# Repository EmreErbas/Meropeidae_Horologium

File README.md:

# Meropeidae Horologium

---
>**This project contains sub-modules. Clone the project recursively**
>
>`git clone --recurse-submodules git@github.com:EmreErbas/Meropeidae_Horologium.git`

---

## Meropeidae Horologium

It is a computer, consisting of a 16x36 resolution screen inspired by [Nixie Tubes](https://en.wikipedia.org/wiki/Nixie_tube), made of single-color LEDs selected according to the wavelength of the light emitted in the excitation of neon gas, and a WiFi-connected controller that drives it.

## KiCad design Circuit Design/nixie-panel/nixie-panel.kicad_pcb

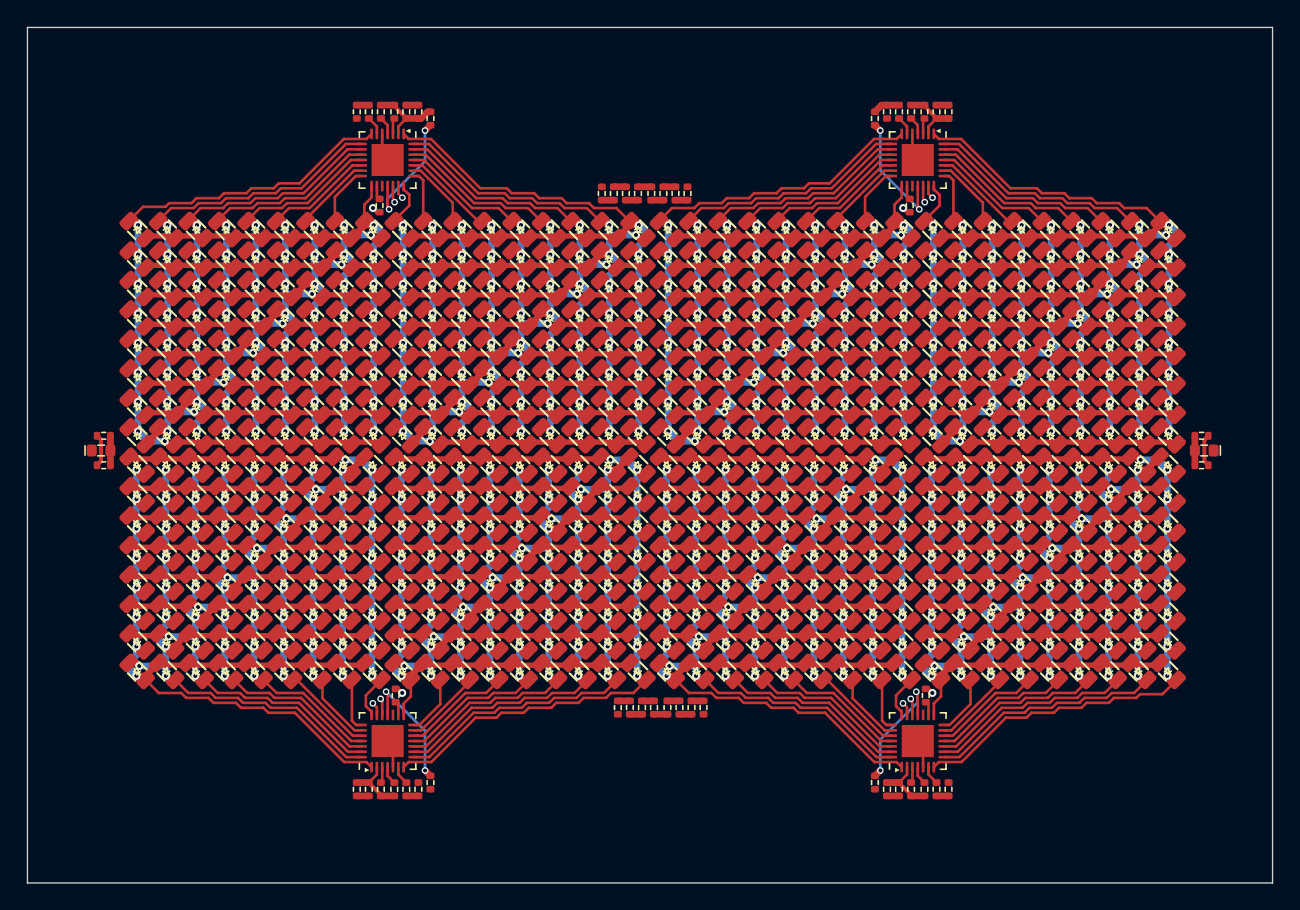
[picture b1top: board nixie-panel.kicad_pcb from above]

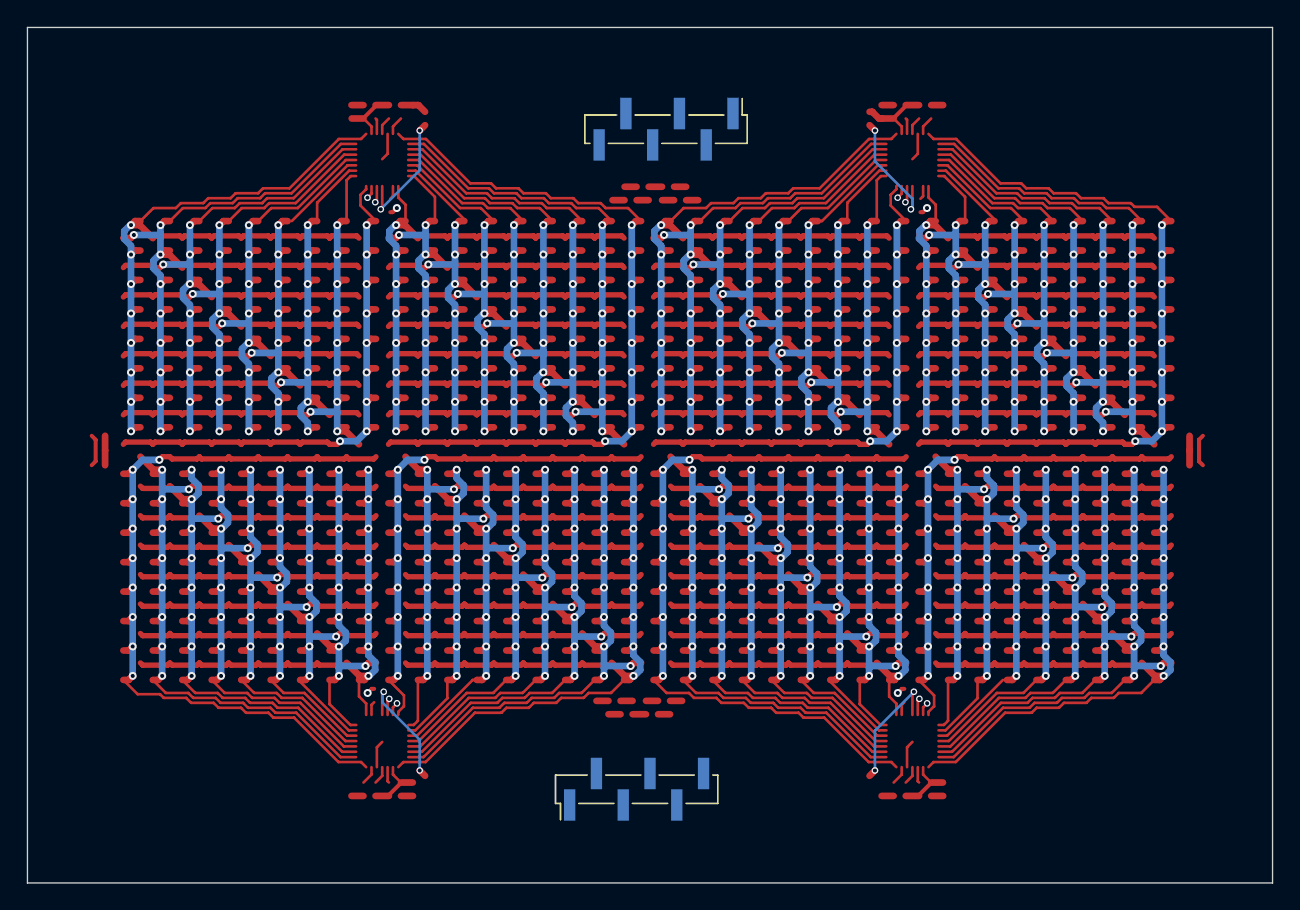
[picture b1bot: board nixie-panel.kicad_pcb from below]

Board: 2 copper layers, 93.0 x 63.9 mm, 636 parts (2 on the bottom side), 108 nets.

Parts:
C24, C25, C26, C30, C34, C38: 1uF; C-0402
C27, C28, C29, C31, C32, C33, C35, C36, C37, C39, C40, C41: 100nF; C-0402
D3, D4, D5, D6, D7, D8, D9, D10, D11, D12, D13, D14, D15, D16, D17, D18, D19, D20, D21, D22, D23, D24, D25, D26, D27, D28, D29, D30, D31, D32, D33, D34, D35, D36, D37, D38, D39, D40, D41, D42, D43, D44, D45, D46, D47, D48, D49, D50, D51, D52, D53, D54, D55, D56, D57, D58, D59, D60, D61, D62, D63, D64, D65, D66, D67, D68, D69, D70, D71, D72, D73, D74, D75, D76, D77, D78, D79, D80, D81, D82, D83, D84, D85, D86, D87, D88, D89, D90, D91, D92, D93, D94, D95, D96, D97, D98, D99, D100, D101, D102, D103, D104, D105, D106, D107, D108, D109, D110, D111, D112, D113, D114, D115, D116, D117, D118, D119, D120, D121, D122, D123, D124, D125, D126, D127, D128, D129, D130, D131, D132, D133, D134, D135, D136, D137, D138, D139, D140, D141, D142, D143, D144, D145, D146, D147, D148, D149, D150, D151, D152, D153, D154, D155, D156, D157, D158, D159, D160, D161, D162, D163, D164, D165, D166, D167, D168, D169, D170, D171, D172, D173, D174, D175, D176, D177, D178, D179, D180, D181, D182, D183, D184, D185, D186, D187, D188, D189, D190, D191, D192, D193, D194, D195, D196, D197, D198, D199, D200, D201, D202, D203, D204, D205, D206, D207, D208, D209, D210, D211, D212, D213, D214, D215, D216, D217, D218, D219, D220, D221, D222, D223, D224, D225, D226, D227, D228, D229, D230, D231, D232, D233, D234, D235, D236, D237, D238, D239, D240, D241, D242, D243, D244, D245, D246, D247, D248, D249, D250, D251, D252, D253, D254, D255, D256, D257, D258, D259, D260, D261, D262, D263, D264, D265, D266, D267, D268, D269, D270, D271, D272, D273, D274, D275, D276, D277, D278, D279, D280, D281, D282, D283, D284, D285, D286, D287, D288, D289, D290, D291, D292, D293, D294, D295, D296, D297, D298, D299, D300, D301, D302, D303, D304, D305, D306, D307, D308, D309, D310, D311, D312, D313, D314, D315, D316, D317, D318, D319, D320, D321, D322, D323, D324, D325, D326, D327, D328, D329, D330, D331, D332, D333, D334, D335, D336, D337, D338, D339, D340, D341, D342, D343, D344, D345, D346, D347, D348, D349, D350, D351, D352, D353, D354, D355, D356, D357, D358, D359, D360, D361, D362, D363, D364, D365, D366, D367, D368, D369, D370, D371, D372, D373, D374, D375, D376, D377, D378, D379, D380, D381, D382, D383, D384, D385, D386, D387, D388, D389, D390, D391, D392, D393, D394, D395, D396, D397, D398, D399, D400, D401, D402, D403, D404, D405, D406, D407, D408, D409, D410, D411, D412, D413, D414, D415, D416, D417, D418, D419, D420, D421, D422, D423, D424, D425, D426, D427, D428, D429, D430, D431, D432, D433, D434, D435, D436, D437, D438, D439, D440, D441, D442, D443, D444, D445, D446, D447, D448, D449, D450, D451, D452, D453, D454, D455, D456, D457, D458, D459, D460, D461, D462, D463, D464, D465, D466, D467, D468, D469, D470, D471, D472, D473, D474, D475, D476, D477, D478, D479, D480, D481, D482, D483, D484, D485, D486, D487, D488, D489, D490, D491, D492, D493, D494, D495, D496, D497, D498, D499, D500, D501, D502, D503, D504, D505, D506, D507, D508, D509, D510, D511, D512, D513, D514, D515, D516, D517, D518, D519, D520, D521, D522, D523, D524, D525, D526, D527, D528, D529, D530, D531, D532, D533, D534, D535, D536, D537, D538, D539, D540, D541, D542, D543, D544, D545, D546, D547, D548, D549, D550, D551, D552, D553, D554, D555, D556, D557, D558, D559, D560, D561, D562, D563, D564, D565, D566, D567, D568, D569, D570, D571, D572, D573, D574, D575, D576, D577, D578: LED_Y_L; LED-0805
J1, J2: Conn_01x06; PinHeader_1x06_P2.00mm_Vertical_SMD_Pin1Left
R15, R16: 2K; R-0402
R17, R18, R19, R20, R27, R28, R29, R30, R37, R38, R39, R40, R47, R48, R49, R50: 10K; R-0402
R21, R22, R31, R32, R41, R42, R51, R52: 1R; R-0402
R25, R35, R45, R55: 0R; R-0402
R26, R36, R46, R56: 18K; R-0402
S1, S2: AmbLightSns; LED-0603
U4, U5, U6, U7: IS31FL3731; QFN-28-EP

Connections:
+3V3: C26.1, C27.1, C28.1, C30.1, C31.1, C32.1, C34.1, C35.1, C36.1, C38.1, C39.1, C40.1, J1.6, J2.6, R17.1, R18.1, R19.1, R20.1, R25.1, R27.1, R28.1, R29.1, R30.1, R35.1, R37.1, R38.1, R39.1, R40.1, R47.1, R48.1, R49.1, R50.1, S1.1, S2.1, U4.2 (VCC), U5.2 (VCC), U6.2 (VCC), U7.2 (VCC)
/I2C0-SCL: J1.3, R22.1, R42.1
/I2C0-SDA: J1.4, R21.1, R41.1
/I2C1-SCL: J2.3, R32.1, R52.1
/I2C1-SDA: J2.4, R31.1, R51.1
/LightSense1: C24.1, J1.2, R15.1, S1.2
/LightSense2: C25.1, J1.5, R16.1, S2.2
/region1/LED Driver/CA1: D3.1 (K), D4.1 (K), D5.1 (K), D6.1 (K), D7.1 (K), D8.1 (K), D9.1 (K), D10.1 (K), D19.2 (A), D35.2 (A), D51.2 (A), D67.2 (A), D83.2 (A), D99.2 (A), D115.2 (A), D131.2 (A), U4.21 (CA1)
/region1/LED Driver/CA2: D3.2 (A), D19.1 (K), D20.1 (K), D21.1 (K), D22.1 (K), D23.1 (K), D24.1 (K), D25.1 (K), D26.1 (K), D36.2 (A), D52.2 (A), D68.2 (A), D84.2 (A), D100.2 (A), D116.2 (A), D132.2 (A), U4.22 (CA2)
/region1/LED Driver/CA3: D4.2 (A), D20.2 (A), D35.1 (K), D36.1 (K), D37.1 (K), D38.1 (K), D39.1 (K), D40.1 (K), D41.1 (K), D42.1 (K), D53.2 (A), D69.2 (A), D85.2 (A), D101.2 (A), D117.2 (A), D133.2 (A), U4.23 (CA3)
/region1/LED Driver/CA4: D5.2 (A), D21.2 (A), D37.2 (A), D51.1 (K), D52.1 (K), D53.1 (K), D54.1 (K), D55.1 (K), D56.1 (K), D57.1 (K), D58.1 (K), D70.2 (A), D86.2 (A), D102.2 (A), D118.2 (A), D134.2 (A), U4.24 (CA4)
/region1/LED Driver/CA5: D6.2 (A), D22.2 (A), D38.2 (A), D54.2 (A), D67.1 (K), D68.1 (K), D69.1 (K), D70.1 (K), D71.1 (K), D72.1 (K), D73.1 (K), D74.1 (K), D87.2 (A), D103.2 (A), D119.2 (A), D135.2 (A), U4.25 (CA5)
/region1/LED Driver/CA6: D7.2 (A), D23.2 (A), D39.2 (A), D55.2 (A), D71.2 (A), D83.1 (K), D84.1 (K), D85.1 (K), D86.1 (K), D87.1 (K), D88.1 (K), D89.1 (K), D90.1 (K), D104.2 (A), D120.2 (A), D136.2 (A), U4.26 (CA6)
/region1/LED Driver/CA7: D8.2 (A), D24.2 (A), D40.2 (A), D56.2 (A), D72.2 (A), D88.2 (A), D99.1 (K), D100.1 (K), D101.1 (K), D102.1 (K), D103.1 (K), D104.1 (K), D105.1 (K), D106.1 (K), D121.2 (A), D137.2 (A), U4.27 (CA7)
/region1/LED Driver/CA8: D9.2 (A), D25.2 (A), D41.2 (A), D57.2 (A), D73.2 (A), D89.2 (A), D105.2 (A), D115.1 (K), D116.1 (K), D117.1 (K), D118.1 (K), D119.1 (K), D120.1 (K), D121.1 (K), D122.1 (K), D138.2 (A), U4.28 (CA8)
/region1/LED Driver/CA9: D10.2 (A), D26.2 (A), D42.2 (A), D58.2 (A), D74.2 (A), D90.2 (A), D106.2 (A), D122.2 (A), D131.1 (K), D132.1 (K), D133.1 (K), D134.1 (K), D135.1 (K), D136.1 (K), D137.1 (K), D138.1 (K), U4.1 (CA9)
/region1/LED Driver/CB1: D11.1 (K), D12.1 (K), D13.1 (K), D14.1 (K), D15.1 (K), D16.1 (K), D17.1 (K), D18.1 (K), D27.2 (A), D43.2 (A), D59.2 (A), D75.2 (A), D91.2 (A), D107.2 (A), D123.2 (A), D139.2 (A), U4.7 (CB1)
/region1/LED Driver/CB2: D11.2 (A), D27.1 (K), D28.1 (K), D29.1 (K), D30.1 (K), D31.1 (K), D32.1 (K), D33.1 (K), D34.1 (K), D44.2 (A), D60.2 (A), D76.2 (A), D92.2 (A), D108.2 (A), D124.2 (A), D140.2 (A), U4.8 (CB2)
/region1/LED Driver/CB3: D12.2 (A), D28.2 (A), D43.1 (K), D44.1 (K), D45.1 (K), D46.1 (K), D47.1 (K), D48.1 (K), D49.1 (K), D50.1 (K), D61.2 (A), D77.2 (A), D93.2 (A), D109.2 (A), D125.2 (A), D141.2 (A), U4.9 (CB3)
/region1/LED Driver/CB4: D13.2 (A), D29.2 (A), D45.2 (A), D59.1 (K), D60.1 (K), D61.1 (K), D62.1 (K), D63.1 (K), D64.1 (K), D65.1 (K), D66.1 (K), D78.2 (A), D94.2 (A), D110.2 (A), D126.2 (A), D142.2 (A), U4.10 (CB4)
/region1/LED Driver/CB5: D14.2 (A), D30.2 (A), D46.2 (A), D62.2 (A), D75.1 (K), D76.1 (K), D77.1 (K), D78.1 (K), D79.1 (K), D80.1 (K), D81.1 (K), D82.1 (K), D95.2 (A), D111.2 (A), D127.2 (A), D143.2 (A), U4.11 (CB5)
/region1/LED Driver/CB6: D15.2 (A), D31.2 (A), D47.2 (A), D63.2 (A), D79.2 (A), D91.1 (K), D92.1 (K), D93.1 (K), D94.1 (K), D95.1 (K), D96.1 (K), D97.1 (K), D98.1 (K), D112.2 (A), D128.2 (A), D144.2 (A), U4.12 (CB6)
/region1/LED Driver/CB7: D16.2 (A), D32.2 (A), D48.2 (A), D64.2 (A), D80.2 (A), D96.2 (A), D107.1 (K), D108.1 (K), D109.1 (K), D110.1 (K), D111.1 (K), D112.1 (K), D113.1 (K), D114.1 (K), D129.2 (A), D145.2 (A), U4.13 (CB7)
/region1/LED Driver/CB8: D17.2 (A), D33.2 (A), D49.2 (A), D65.2 (A), D81.2 (A), D97.2 (A), D113.2 (A), D123.1 (K), D124.1 (K), D125.1 (K), D126.1 (K), D127.1 (K), D128.1 (K), D129.1 (K), D130.1 (K), D146.2 (A), U4.14 (CB8)
/region1/LED Driver/CB9: D18.2 (A), D34.2 (A), D50.2 (A), D66.2 (A), D82.2 (A), D98.2 (A), D114.2 (A), D130.2 (A), D139.1 (K), D140.1 (K), D141.1 (K), D142.1 (K), D143.1 (K), D144.1 (K), D145.1 (K), D146.1 (K), U4.15 (CB9)
/region1/LED Driver/INTB: R18.2, U4.4 (INTB)
/region1/LED Driver/SDB: R17.2, U4.3 (SDB)
/region2/LED Driver/CA1: D147.1 (K), D148.1 (K), D149.1 (K), D150.1 (K), D151.1 (K), D152.1 (K), D153.1 (K), D154.1 (K), D163.2 (A), D179.2 (A), D195.2 (A), D211.2 (A), D227.2 (A), D243.2 (A), D259.2 (A), D275.2 (A), U5.21 (CA1)
/region2/LED Driver/CA2: D147.2 (A), D163.1 (K), D164.1 (K), D165.1 (K), D166.1 (K), D167.1 (K), D168.1 (K), D169.1 (K), D170.1 (K), D180.2 (A), D196.2 (A), D212.2 (A), D228.2 (A), D244.2 (A), D260.2 (A), D276.2 (A), U5.22 (CA2)
/region2/LED Driver/CA3: D148.2 (A), D164.2 (A), D179.1 (K), D180.1 (K), D181.1 (K), D182.1 (K), D183.1 (K), D184.1 (K), D185.1 (K), D186.1 (K), D197.2 (A), D213.2 (A), D229.2 (A), D245.2 (A), D261.2 (A), D277.2 (A), U5.23 (CA3)
/region2/LED Driver/CA4: D149.2 (A), D165.2 (A), D181.2 (A), D195.1 (K), D196.1 (K), D197.1 (K), D198.1 (K), D199.1 (K), D200.1 (K), D201.1 (K), D202.1 (K), D214.2 (A), D230.2 (A), D246.2 (A), D262.2 (A), D278.2 (A), U5.24 (CA4)
/region2/LED Driver/CA5: D150.2 (A), D166.2 (A), D182.2 (A), D198.2 (A), D211.1 (K), D212.1 (K), D213.1 (K), D214.1 (K), D215.1 (K), D216.1 (K), D217.1 (K), D218.1 (K), D231.2 (A), D247.2 (A), D263.2 (A), D279.2 (A), U5.25 (CA5)
/region2/LED Driver/CA6: D151.2 (A), D167.2 (A), D183.2 (A), D199.2 (A), D215.2 (A), D227.1 (K), D228.1 (K), D229.1 (K), D230.1 (K), D231.1 (K), D232.1 (K), D233.1 (K), D234.1 (K), D248.2 (A), D264.2 (A), D280.2 (A), U5.26 (CA6)
/region2/LED Driver/CA7: D152.2 (A), D168.2 (A), D184.2 (A), D200.2 (A), D216.2 (A), D232.2 (A), D243.1 (K), D244.1 (K), D245.1 (K), D246.1 (K), D247.1 (K), D248.1 (K), D249.1 (K), D250.1 (K), D265.2 (A), D281.2 (A), U5.27 (CA7)
/region2/LED Driver/CA8: D153.2 (A), D169.2 (A), D185.2 (A), D201.2 (A), D217.2 (A), D233.2 (A), D249.2 (A), D259.1 (K), D260.1 (K), D261.1 (K), D262.1 (K), D263.1 (K), D264.1 (K), D265.1 (K), D266.1 (K), D282.2 (A), U5.28 (CA8)
/region2/LED Driver/CA9: D154.2 (A), D170.2 (A), D186.2 (A), D202.2 (A), D218.2 (A), D234.2 (A), D250.2 (A), D266.2 (A), D275.1 (K), D276.1 (K), D277.1 (K), D278.1 (K), D279.1 (K), D280.1 (K), D281.1 (K), D282.1 (K), U5.1 (CA9)
/region2/LED Driver/CB1: D155.1 (K), D156.1 (K), D157.1 (K), D158.1 (K), D159.1 (K), D160.1 (K), D161.1 (K), D162.1 (K), D171.2 (A), D187.2 (A), D203.2 (A), D219.2 (A), D235.2 (A), D251.2 (A), D267.2 (A), D283.2 (A), U5.7 (CB1)
/region2/LED Driver/CB2: D155.2 (A), D171.1 (K), D172.1 (K), D173.1 (K), D174.1 (K), D175.1 (K), D176.1 (K), D177.1 (K), D178.1 (K), D188.2 (A), D204.2 (A), D220.2 (A), D236.2 (A), D252.2 (A), D268.2 (A), D284.2 (A), U5.8 (CB2)
/region2/LED Driver/CB3: D156.2 (A), D172.2 (A), D187.1 (K), D188.1 (K), D189.1 (K), D190.1 (K), D191.1 (K), D192.1 (K), D193.1 (K), D194.1 (K), D205.2 (A), D221.2 (A), D237.2 (A), D253.2 (A), D269.2 (A), D285.2 (A), U5.9 (CB3)
/region2/LED Driver/CB4: D157.2 (A), D173.2 (A), D189.2 (A), D203.1 (K), D204.1 (K), D205.1 (K), D206.1 (K), D207.1 (K), D208.1 (K), D209.1 (K), D210.1 (K), D222.2 (A), D238.2 (A), D254.2 (A), D270.2 (A), D286.2 (A), U5.10 (CB4)
/region2/LED Driver/CB5: D158.2 (A), D174.2 (A), D190.2 (A), D206.2 (A), D219.1 (K), D220.1 (K), D221.1 (K), D222.1 (K), D223.1 (K), D224.1 (K), D225.1 (K), D226.1 (K), D239.2 (A), D255.2 (A), D271.2 (A), D287.2 (A), U5.11 (CB5)
/region2/LED Driver/CB6: D159.2 (A), D175.2 (A), D191.2 (A), D207.2 (A), D223.2 (A), D235.1 (K), D236.1 (K), D237.1 (K), D238.1 (K), D239.1 (K), D240.1 (K), D241.1 (K), D242.1 (K), D256.2 (A), D272.2 (A), D288.2 (A), U5.12 (CB6)
/region2/LED Driver/CB7: D160.2 (A), D176.2 (A), D192.2 (A), D208.2 (A), D224.2 (A), D240.2 (A), D251.1 (K), D252.1 (K), D253.1 (K), D254.1 (K), D255.1 (K), D256.1 (K), D257.1 (K), D258.1 (K), D273.2 (A), D289.2 (A), U5.13 (CB7)
/region2/LED Driver/CB8: D161.2 (A), D177.2 (A), D193.2 (A), D209.2 (A), D225.2 (A), D241.2 (A), D257.2 (A), D267.1 (K), D268.1 (K), D269.1 (K), D270.1 (K), D271.1 (K), D272.1 (K), D273.1 (K), D274.1 (K), D290.2 (A), U5.14 (CB8)
/region2/LED Driver/CB9: D162.2 (A), D178.2 (A), D194.2 (A), D210.2 (A), D226.2 (A), D242.2 (A), D258.2 (A), D274.2 (A), D283.1 (K), D284.1 (K), D285.1 (K), D286.1 (K), D287.1 (K), D288.1 (K), D289.1 (K), D290.1 (K), U5.15 (CB9)
/region2/LED Driver/INTB: R28.2, U5.4 (INTB)
/region2/LED Driver/SDB: R27.2, U5.3 (SDB)
/region3/LED Driver/CA1: D291.1 (K), D292.1 (K), D293.1 (K), D294.1 (K), D295.1 (K), D296.1 (K), D297.1 (K), D298.1 (K), D307.2 (A), D323.2 (A), D339.2 (A), D355.2 (A), D371.2 (A), D387.2 (A), D403.2 (A), D419.2 (A), U6.21 (CA1)
/region3/LED Driver/CA2: D291.2 (A), D307.1 (K), D308.1 (K), D309.1 (K), D310.1 (K), D311.1 (K), D312.1 (K), D313.1 (K), D314.1 (K), D324.2 (A), D340.2 (A), D356.2 (A), D372.2 (A), D388.2 (A), D404.2 (A), D420.2 (A), U6.22 (CA2)
/region3/LED Driver/CA3: D292.2 (A), D308.2 (A), D323.1 (K), D324.1 (K), D325.1 (K), D326.1 (K), D327.1 (K), D328.1 (K), D329.1 (K), D330.1 (K), D341.2 (A), D357.2 (A), D373.2 (A), D389.2 (A), D405.2 (A), D421.2 (A), U6.23 (CA3)
/region3/LED Driver/CA4: D293.2 (A), D309.2 (A), D325.2 (A), D339.1 (K), D340.1 (K), D341.1 (K), D342.1 (K), D343.1 (K), D344.1 (K), D345.1 (K), D346.1 (K), D358.2 (A), D374.2 (A), D390.2 (A), D406.2 (A), D422.2 (A), U6.24 (CA4)
/region3/LED Driver/CA5: D294.2 (A), D310.2 (A), D326.2 (A), D342.2 (A), D355.1 (K), D356.1 (K), D357.1 (K), D358.1 (K), D359.1 (K), D360.1 (K), D361.1 (K), D362.1 (K), D375.2 (A), D391.2 (A), D407.2 (A), D423.2 (A), U6.25 (CA5)
/region3/LED Driver/CA6: D295.2 (A), D311.2 (A), D327.2 (A), D343.2 (A), D359.2 (A), D371.1 (K), D372.1 (K), D373.1 (K), D374.1 (K), D375.1 (K), D376.1 (K), D377.1 (K), D378.1 (K), D392.2 (A), D408.2 (A), D424.2 (A), U6.26 (CA6)
/region3/LED Driver/CA7: D296.2 (A), D312.2 (A), D328.2 (A), D344.2 (A), D360.2 (A), D376.2 (A), D387.1 (K), D388.1 (K), D389.1 (K), D390.1 (K), D391.1 (K), D392.1 (K), D393.1 (K), D394.1 (K), D409.2 (A), D425.2 (A), U6.27 (CA7)
/region3/LED Driver/CA8: D297.2 (A), D313.2 (A), D329.2 (A), D345.2 (A), D361.2 (A), D377.2 (A), D393.2 (A), D403.1 (K), D404.1 (K), D405.1 (K), D406.1 (K), D407.1 (K), D408.1 (K), D409.1 (K), D410.1 (K), D426.2 (A), U6.28 (CA8)
/region3/LED Driver/CA9: D298.2 (A), D314.2 (A), D330.2 (A), D346.2 (A), D362.2 (A), D378.2 (A), D394.2 (A), D410.2 (A), D419.1 (K), D420.1 (K), D421.1 (K), D422.1 (K), D423.1 (K), D424.1 (K), D425.1 (K), D426.1 (K), U6.1 (CA9)
/region3/LED Driver/CB1: D299.1 (K), D300.1 (K), D301.1 (K), D302.1 (K), D303.1 (K), D304.1 (K), D305.1 (K), D306.1 (K), D315.2 (A), D331.2 (A), D347.2 (A), D363.2 (A), D379.2 (A), D395.2 (A), D411.2 (A), D427.2 (A), U6.7 (CB1)
/region3/LED Driver/CB2: D299.2 (A), D315.1 (K), D316.1 (K), D317.1 (K), D318.1 (K), D319.1 (K), D320.1 (K), D321.1 (K), D322.1 (K), D332.2 (A), D348.2 (A), D364.2 (A), D380.2 (A), D396.2 (A), D412.2 (A), D428.2 (A), U6.8 (CB2)
/region3/LED Driver/CB3: D300.2 (A), D316.2 (A), D331.1 (K), D332.1 (K), D333.1 (K), D334.1 (K), D335.1 (K), D336.1 (K), D337.1 (K), D338.1 (K), D349.2 (A), D365.2 (A), D381.2 (A), D397.2 (A), D413.2 (A), D429.2 (A), U6.9 (CB3)
/region3/LED Driver/CB4: D301.2 (A), D317.2 (A), D333.2 (A), D347.1 (K), D348.1 (K), D349.1 (K), D350.1 (K), D351.1 (K), D352.1 (K), D353.1 (K), D354.1 (K), D366.2 (A), D382.2 (A), D398.2 (A), D414.2 (A), D430.2 (A), U6.10 (CB4)
/region3/LED Driver/CB5: D302.2 (A), D318.2 (A), D334.2 (A), D350.2 (A), D363.1 (K), D364.1 (K), D365.1 (K), D366.1 (K), D367.1 (K), D368.1 (K), D369.1 (K), D370.1 (K), D383.2 (A), D399.2 (A), D415.2 (A), D431.2 (A), U6.11 (CB5)
/region3/LED Driver/CB6: D303.2 (A), D319.2 (A), D335.2 (A), D351.2 (A), D367.2 (A), D379.1 (K), D380.1 (K), D381.1 (K), D382.1 (K), D383.1 (K), D384.1 (K), D385.1 (K), D386.1 (K), D400.2 (A), D416.2 (A), D432.2 (A), U6.12 (CB6)
/region3/LED Driver/CB7: D304.2 (A), D320.2 (A), D336.2 (A), D352.2 (A), D368.2 (A), D384.2 (A), D395.1 (K), D396.1 (K), D397.1 (K), D398.1 (K), D399.1 (K), D400.1 (K), D401.1 (K), D402.1 (K), D417.2 (A), D433.2 (A), U6.13 (CB7)
/region3/LED Driver/CB8: D305.2 (A), D321.2 (A), D337.2 (A), D353.2 (A), D369.2 (A), D385.2 (A), D401.2 (A), D411.1 (K), D412.1 (K), D413.1 (K), D414.1 (K), D415.1 (K), D416.1 (K), D417.1 (K), D418.1 (K), D434.2 (A), U6.14 (CB8)
/region3/LED Driver/CB9: D306.2 (A), D322.2 (A), D338.2 (A), D354.2 (A), D370.2 (A), D386.2 (A), D402.2 (A), D418.2 (A), D427.1 (K), D428.1 (K), D429.1 (K), D430.1 (K), D431.1 (K), D432.1 (K), D433.1 (K), D434.1 (K), U6.15 (CB9)
/region3/LED Driver/INTB: R38.2, U6.4 (INTB)
/region3/LED Driver/SDB: R37.2, U6.3 (SDB)
/region4/LED Driver/CA1: D435.1 (K), D436.1 (K), D437.1 (K), D438.1 (K), D439.1 (K), D440.1 (K), D441.1 (K), D442.1 (K), D451.2 (A), D467.2 (A), D483.2 (A), D499.2 (A), D515.2 (A), D531.2 (A), D547.2 (A), D563.2 (A), U7.21 (CA1)
/region4/LED Driver/CA2: D435.2 (A), D451.1 (K), D452.1 (K), D453.1 (K), D454.1 (K), D455.1 (K), D456.1 (K), D457.1 (K), D458.1 (K), D468.2 (A), D484.2 (A), D500.2 (A), D516.2 (A), D532.2 (A), D548.2 (A), D564.2 (A), U7.22 (CA2)
/region4/LED Driver/CA3: D436.2 (A), D452.2 (A), D467.1 (K), D468.1 (K), D469.1 (K), D470.1 (K), D471.1 (K), D472.1 (K), D473.1 (K), D474.1 (K), D485.2 (A), D501.2 (A), D517.2 (A), D533.2 (A), D549.2 (A), D565.2 (A), U7.23 (CA3)
/region4/LED Driver/CA4: D437.2 (A), D453.2 (A), D469.2 (A), D483.1 (K), D484.1 (K), D485.1 (K), D486.1 (K), D487.1 (K), D488.1 (K), D489.1 (K), D490.1 (K), D502.2 (A), D518.2 (A), D534.2 (A), D550.2 (A), D566.2 (A), U7.24 (CA4)
/region4/LED Driver/CA5: D438.2 (A), D454.2 (A), D470.2 (A), D486.2 (A), D499.1 (K), D500.1 (K), D501.1 (K), D502.1 (K), D503.1 (K), D504.1 (K), D505.1 (K), D506.1 (K), D519.2 (A), D535.2 (A), D551.2 (A), D567.2 (A), U7.25 (CA5)
/region4/LED Driver/CA6: D439.2 (A), D455.2 (A), D471.2 (A), D487.2 (A), D503.2 (A), D515.1 (K), D516.1 (K), D517.1 (K), D518.1 (K), D519.1 (K), D520.1 (K), D521.1 (K), D522.1 (K), D536.2 (A), D552.2 (A), D568.2 (A), U7.26 (CA6)
/region4/LED Driver/CA7: D440.2 (A), D456.2 (A), D472.2 (A), D488.2 (A), D504.2 (A), D520.2 (A), D531.1 (K), D532.1 (K), D533.1 (K), D534.1 (K), D535.1 (K), D536.1 (K), D537.1 (K), D538.1 (K), D553.2 (A), D569.2 (A), U7.27 (CA7)
/region4/LED Driver/CA8: D441.2 (A), D457.2 (A), D473.2 (A), D489.2 (A), D505.2 (A), D521.2 (A), D537.2 (A), D547.1 (K), D548.1 (K), D549.1 (K), D550.1 (K), D551.1 (K), D552.1 (K), D553.1 (K), D554.1 (K), D570.2 (A), U7.28 (CA8)
/region4/LED Driver/CA9: D442.2 (A), D458.2 (A), D474.2 (A), D490.2 (A), D506.2 (A), D522.2 (A), D538.2 (A), D554.2 (A), D563.1 (K), D564.1 (K), D565.1 (K), D566.1 (K), D567.1 (K), D568.1 (K), D569.1 (K), D570.1 (K), U7.1 (CA9)
/region4/LED Driver/CB1: D443.1 (K), D444.1 (K), D445.1 (K), D446.1 (K), D447.1 (K), D448.1 (K), D449.1 (K), D450.1 (K), D459.2 (A), D475.2 (A), D491.2 (A), D507.2 (A), D523.2 (A), D539.2 (A), D555.2 (A), D571.2 (A), U7.7 (CB1)
/region4/LED Driver/CB2: D443.2 (A), D459.1 (K), D460.1 (K), D461.1 (K), D462.1 (K), D463.1 (K), D464.1 (K), D465.1 (K), D466.1 (K), D476.2 (A), D492.2 (A), D508.2 (A), D524.2 (A), D540.2 (A), D556.2 (A), D572.2 (A), U7.8 (CB2)
/region4/LED Driver/CB3: D444.2 (A), D460.2 (A), D475.1 (K), D476.1 (K), D477.1 (K), D478.1 (K), D479.1 (K), D480.1 (K), D481.1 (K), D482.1 (K), D493.2 (A), D509.2 (A), D525.2 (A), D541.2 (A), D557.2 (A), D573.2 (A), U7.9 (CB3)
/region4/LED Driver/CB4: D445.2 (A), D461.2 (A), D477.2 (A), D491.1 (K), D492.1 (K), D493.1 (K), D494.1 (K), D495.1 (K), D496.1 (K), D497.1 (K), D498.1 (K), D510.2 (A), D526.2 (A), D542.2 (A), D558.2 (A), D574.2 (A), U7.10 (CB4)
/region4/LED Driver/CB5: D446.2 (A), D462.2 (A), D478.2 (A), D494.2 (A), D507.1 (K), D508.1 (K), D509.1 (K), D510.1 (K), D511.1 (K), D512.1 (K), D513.1 (K), D514.1 (K), D527.2 (A), D543.2 (A), D559.2 (A), D575.2 (A), U7.11 (CB5)
/region4/LED Driver/CB6: D447.2 (A), D463.2 (A), D479.2 (A), D495.2 (A), D511.2 (A), D523.1 (K), D524.1 (K), D525.1 (K), D526.1 (K), D527.1 (K), D528.1 (K), D529.1 (K), D530.1 (K), D544.2 (A), D560.2 (A), D576.2 (A), U7.12 (CB6)
/region4/LED Driver/CB7: D448.2 (A), D464.2 (A), D480.2 (A), D496.2 (A), D512.2 (A), D528.2 (A), D539.1 (K), D540.1 (K), D541.1 (K), D542.1 (K), D543.1 (K), D544.1 (K), D545.1 (K), D546.1 (K), D561.2 (A), D577.2 (A), U7.13 (CB7)
/region4/LED Driver/CB8: D449.2 (A), D465.2 (A), D481.2 (A), D497.2 (A), D513.2 (A), D529.2 (A), D545.2 (A), D555.1 (K), D556.1 (K), D557.1 (K), D558.1 (K), D559.1 (K), D560.1 (K), D561.1 (K), D562.1 (K), D578.2 (A), U7.14 (CB8)
/region4/LED Driver/CB9: D450.2 (A), D466.2 (A), D482.2 (A), D498.2 (A), D514.2 (A), D530.2 (A), D546.2 (A), D562.2 (A), D571.1 (K), D572.1 (K), D573.1 (K), D574.1 (K), D575.1 (K), D576.1 (K), D577.1 (K), D578.1 (K), U7.15 (CB9)
/region4/LED Driver/INTB: R48.2, U7.4 (INTB)
/region4/LED Driver/SDB: R47.2, U7.3 (SDB)
GND: C24.2, C25.2, C26.2, C27.2, C28.2, C29.2, C30.2, C31.2, C32.2, C33.2, C34.2, C35.2, C36.2, C37.2, C38.2, C39.2, C40.2, C41.2, J1.1, J2.1, R15.2, R16.2, R26.1, R36.1, R45.1, R46.1, R55.1, R56.1, U4.5 (GND), U4.29 (PAD), U5.5 (GND), U5.29 (PAD), U6.5 (GND), U6.29 (PAD), U7.5 (GND), U7.29 (PAD)
unnamed: C29.1, U4.16 (C_FILT)
unnamed: C33.1, U5.16 (C_FILT)
unnamed: C37.1, U6.16 (C_FILT)
unnamed: C41.1, U7.16 (C_FILT)
unnamed: R19.2, R22.2, U4.20 (SCL)
unnamed: R20.2, R21.2, U4.19 (SDA)
unnamed: R25.2, U4.18 (ADDR)
unnamed: R26.2, U4.6 (R_EXT)
unnamed: R29.2, R32.2, U5.20 (SCL)
unnamed: R30.2, R31.2, U5.19 (SDA)
unnamed: R35.2, U5.18 (ADDR)
unnamed: R36.2, U5.6 (R_EXT)
unnamed: R39.2, R42.2, U6.20 (SCL)
unnamed: R40.2, R41.2, U6.19 (SDA)
unnamed: R45.2, U6.18 (ADDR)
unnamed: R46.2, U6.6 (R_EXT)
unnamed: R49.2, R52.2, U7.20 (SCL)
unnamed: R50.2, R51.2, U7.19 (SDA)
unnamed: R55.2, U7.18 (ADDR)
unnamed: R56.2, U7.6 (R_EXT)
